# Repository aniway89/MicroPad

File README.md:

# Micro PAD — Retro PCB Design

A small macropad project designed using KiCad and FreeCAD. This repository contains the PCB design, schematic, 3D model, and related resources used to build the project.

## Project Files

- **PCB schematic/** — PCB schematic and related design files.
- **PCB schematic/FreeCAD Files/** — FreeCAD design files.
- **PCB schematic/PCB STEP file/** — STEP models related to the PCB.
- **Micro PAD free CAD IMAGES/** — Screenshots of the 3D model and CAD design.
- **Resources/** — Additional resources used in the project, including key, switch, and microcontroller 3D models.
- **Micro PAD OBJ.obj** — 3D model exported in OBJ format.
- **Micro PAD STEP.step** — 3D model exported in STEP format.

## Software Used

- KiCad — Schematic and PCB design.
- FreeCAD — 3D modelling and enclosure design.

## Resources

The `Resources` folder contains supporting models and files used during the design process, including:

- Key models
- Switch STEP files
- Seeed Studio XIAO SAMD21 3D model
- KiCad-related resources

These files are used to help position and check the components in the 3D design.

## Status

The project design stage is completed. PCB and enclosure designs are being developed and checked.

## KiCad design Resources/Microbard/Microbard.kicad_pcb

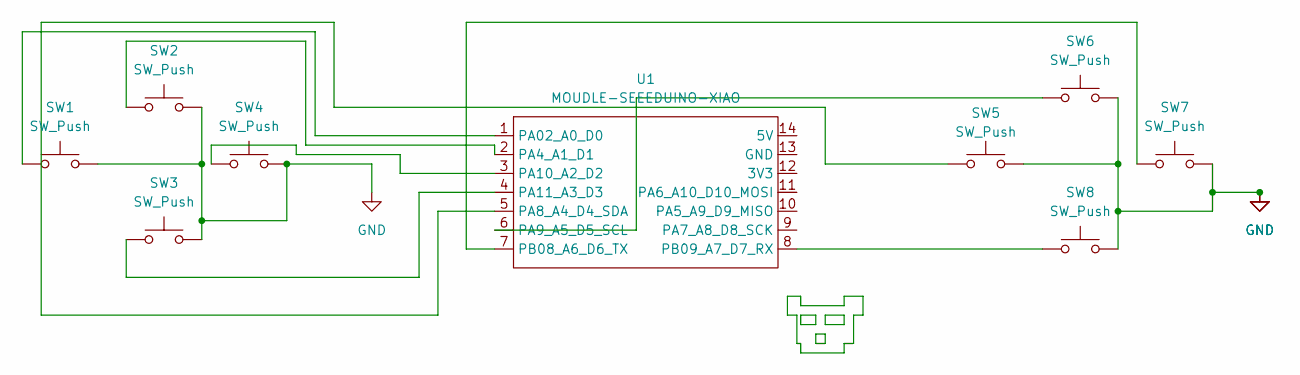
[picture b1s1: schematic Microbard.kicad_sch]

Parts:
SW1, SW2, SW3, SW4, SW5, SW6, SW7, SW8: SW_Push; SW_Cherry_MX_1.00u_PCB
U1: MOUDLE-SEEEDUINO-XIAO; XIAO-Generic-Hybrid-14P-2.54-21X17.8MM

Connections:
GND: SW1.2, SW2.2, SW3.2, SW4.2, SW5.2, SW6.2, SW7.2, SW8.2
unnamed: SW1.1, U1.1 (PA02_A0_D0)
unnamed: SW2.1, U1.2 (PA4_A1_D1)
unnamed: SW5.1, U1.5 (PA8_A4_D4_SDA)
unnamed: SW6.1, U1.6 (PA9_A5_D5_SCL)
unnamed: SW4.1, U1.3 (PA10_A2_D2)
unnamed: SW3.1, U1.4 (PA11_A3_D3)
unnamed: SW7.1, U1.7 (PB08_A6_D6_TX)
unnamed: SW8.1, U1.8 (PB09_A7_D7_RX)

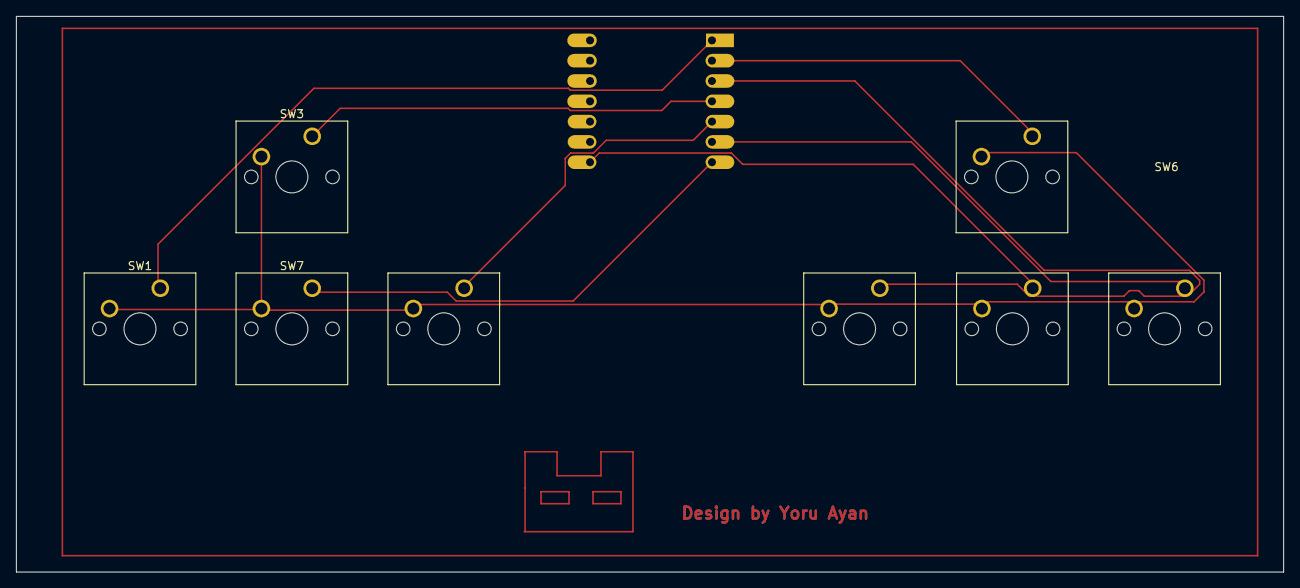
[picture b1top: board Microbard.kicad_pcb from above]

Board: 2 copper layers, 158.5 x 69.5 mm, 9 parts (1 on the bottom side), 9 nets.
